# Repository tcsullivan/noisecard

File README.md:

# NoiseCard

NoiseCard is an attempt to build a dead easy tool for monitoring ambient noise levels. The ultra-low-power microcontroller takes periodic decibel measurements while powered on, using blinking LEDs for indication. The circuit requires only a few milliwatts to run, enabling it to run off of direct solar power without a battery (though some large capacitors provide a small reserve).

Ambient noise levels in populated areas, especially North America, can often exceed what is considered safe for our ears, with prolonged exposure leading to lasting impacts on our health. Through a tool like the NoiseCard, people can become more aware of the noisy environments they're living in (and potentially take action to reduce excess noise exposure).

## Building the source

You need:

* [ChibiOS sources](https://www.chibios.org/dokuwiki/doku.php)
* The arm-none-eabi GCC toolchain (through your distro or from [ARM developer](https://developer.arm.com/downloads/-/gnu-rm))
* [GNU Make](https://www.gnu.org/software/make/)
* [OpenOCD](https://openocd.org/) or another tool to program the microcontroller
* [KiCAD](https://www.kicad.org/) if you wish to work with the hardware files

Extract ChibiOS to a folder, edit the `Makefile` so CHIBIOS points to that folder, then run `make`.

### Flashing the card

You'll need a 6-pin Tag-Connect cable (e.g. [TC2030-CTX-NL](https://www.tag-connect.com/product/tc2030-ctx-nl-6-pin-no-legs-cable-with-10-pin-micro-connector-for-cortex-processors)), compatible programmer, and OpenOCD. Power up the card and run the following command (using the appropriate interface scripts for your programmer):

```
openocd -f interface/ftdi/olimex-arm-usb-ocd-h.cfg -f interface/ftdi/olimex-arm-jtag-swd.cfg -f target/stm32g0x.cfg -c "program build/ch.hex verify reset exit"
```

## Credits

* [ESP32-I2S-SLM](https://hackaday.io/project/166867-esp32-i2s-slm) for a starting point with accurate decibel-measuring code.
* [Qfplib](https://www.quinapalus.com/qfplib.html) for providing optimized floating-point code for the Cortex-M0+ microcontroller.
* ChibiOS for providing an awesome RTOS and HAL that made firmware porting and device configuration a breeze.

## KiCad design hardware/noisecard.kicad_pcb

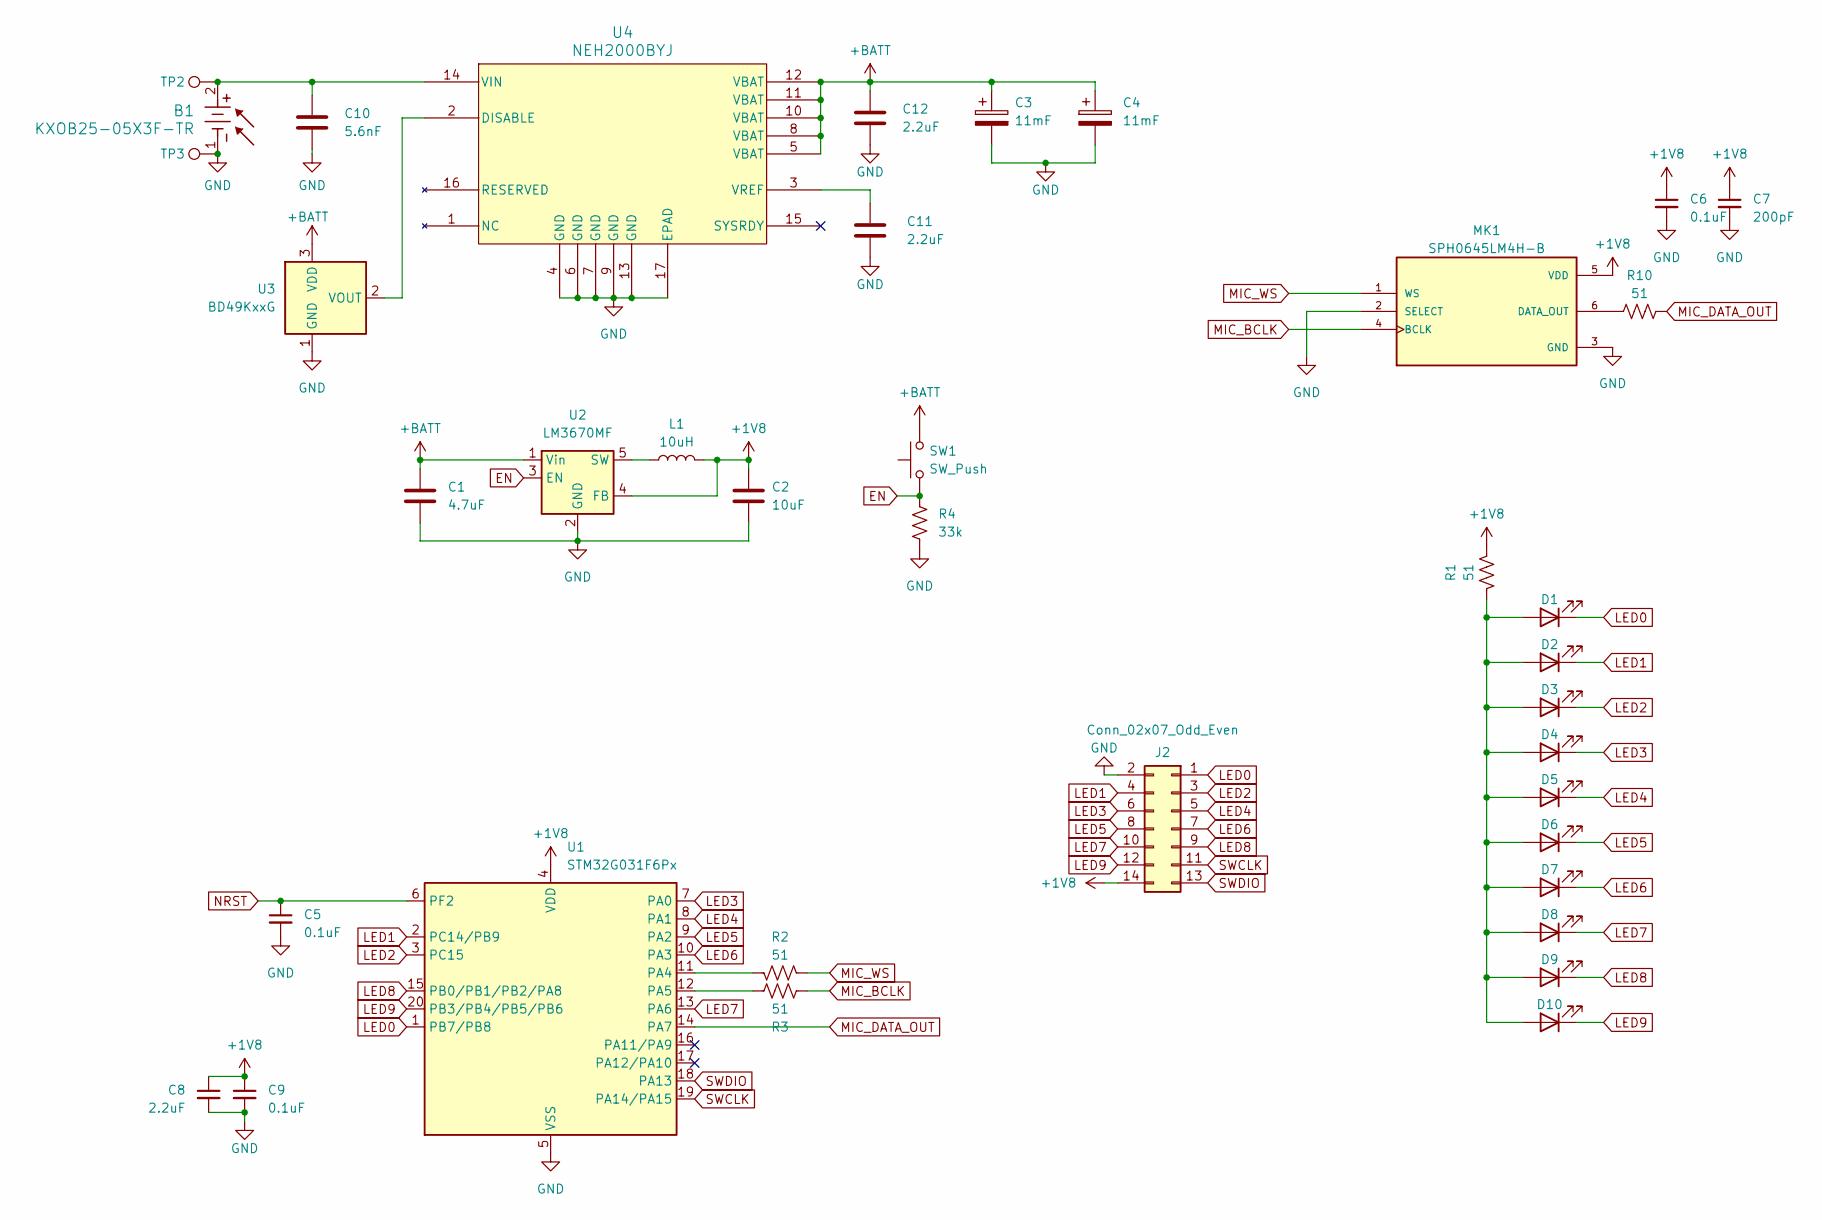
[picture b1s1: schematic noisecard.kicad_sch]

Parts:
B1: KXOB25-05X3F-TR; KXOB25-02X8F-TR_IXY; Part Number KXOB25-05X3F-TR
C1: 4.7uF; C_0805_2012Metric; Part Number CL21A475KAQNNNE
C2: 10uF; C_0805_2012Metric; Part Number CL21A106KOQNNNE
C3, C4: 11mF; C_1210_3225Metric; Part Number CPH3225A
C5, C6, C9: 0.1uF; C_0603_1608Metric; Part Number CC0603KRX7R6BB104
C7: 200pF; C_0603_1608Metric; Part Number 06033A201FAT2A
C8, C11, C12: 2.2uF; C_0805_2012Metric; Part Number CL21A225KBFNNNE
C10: 5.6nF; C_0603_1608Metric
D1, D2, D3, D4, D5, D6, D7, D8, D9, D10: LED; LED_0603_1608Metric; Part Number APTD1608LSURCK
J2: Conn_02x07_Odd_Even; PinHeader_2x07_P2.54mm_Vertical
L1: 10uH; L_0805_2012Metric; Part Number MLZ2012N100LT000
MK1: SPH0645LM4H-B; MIC_SPH0645LM4H-B; Part Number SPH0645LM4H-B
R1, R2, R3, R10: 51; R_0603_1608Metric; Part Number RC0603JR-0751RL
R4: 33k; R_0603_1608Metric
SW1: SW_Push; SW_SPST_EVQP0
TP2, TP3: TestPoint; TestPoint_THTPad_3.0x3.0mm_Drill1.5mm
U1: STM32G031F6Px; TSSOP-20_4.4x6.5mm_P0.65mm; Part Number STM32G031F6P6
U2: LM3670MF; TSOT-23-5; Part Number LM3670MF-1.8/NOPB
U3: BD49KxxG; SOT-23
U4: NEH2000BYJ; HWQFN16_SOT8076-1_NEX; Part Number NEH2000BYJ

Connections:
+1V8: C2.1, C6.1, C7.1, C8.1, C9.1, J2.14, L1.2, MK1.5 (VDD), R1.1, U1.4 (VDD), U2.4 (FB)
+BATT: C1.1, C3.1, C4.1, C12.1, SW1.2, U2.1 (Vin), U3.3 (VDD), U4.5 (VBAT), U4.8 (VBAT), U4.10 (VBAT), U4.11 (VBAT), U4.12 (VBAT)
EN: R4.2, SW1.1, U2.3 (EN)
GND: B1.1, C1.2, C2.2, C3.2, C4.2, C5.2, C6.2, C7.2, C8.2, C9.2, C10.2, C11.2, C12.2, J2.2, MK1.2 (SELECT), MK1.3 (GND), R4.1, TP3.1, U1.5 (VSS), U2.2 (GND), U3.1 (GND), U4.4 (GND), U4.6 (GND), U4.7 (GND), U4.9 (GND), U4.13 (GND), U4.17 (EPAD)
LED0: D1.1 (K), J2.1, U1.1 (PB7/PB8)
LED1: D2.1 (K), J2.4, U1.2 (PC14/PB9)
LED2: D3.1 (K), J2.3, U1.3 (PC15)
LED3: D4.1 (K), J2.6, U1.7 (PA0)
LED4: D5.1 (K), J2.5, U1.8 (PA1)
LED5: D6.1 (K), J2.8, U1.9 (PA2)
LED6: D7.1 (K), J2.7, U1.10 (PA3)
LED7: D8.1 (K), J2.10, U1.13 (PA6)
LED8: D9.1 (K), J2.9, U1.15 (PB0/PB1/PB2/PA8)
LED9: D10.1 (K), J2.12, U1.20 (PB3/PB4/PB5/PB6)
MIC_BCLK: MK1.4 (BCLK), R3.1
MIC_DATA_OUT: R10.2, U1.14 (PA7)
MIC_WS: MK1.1 (WS), R2.1
NRST: C5.1, U1.6 (PF2)
unnamed: D1.2 (A), D2.2 (A), D3.2 (A), D4.2 (A), D5.2 (A), D6.2 (A), D7.2 (A), D8.2 (A), D9.2 (A), D10.2 (A), R1.2
unnamed: MK1.6 (DATA_OUT), R10.1
unnamed: R2.2, U1.11 (PA4)
unnamed: R3.2, U1.12 (PA5)
unnamed: L1.1, U2.5 (SW)
unnamed: U3.2 (VOUT), U4.2 (DISABLE)
unnamed: B1.2, C10.1, TP2.1, U4.14 (VIN)
unnamed: C11.1, U4.3 (VREF)
SWCLK: J2.11, U1.19 (PA14/PA15)
SWDIO: J2.13, U1.18 (PA13)

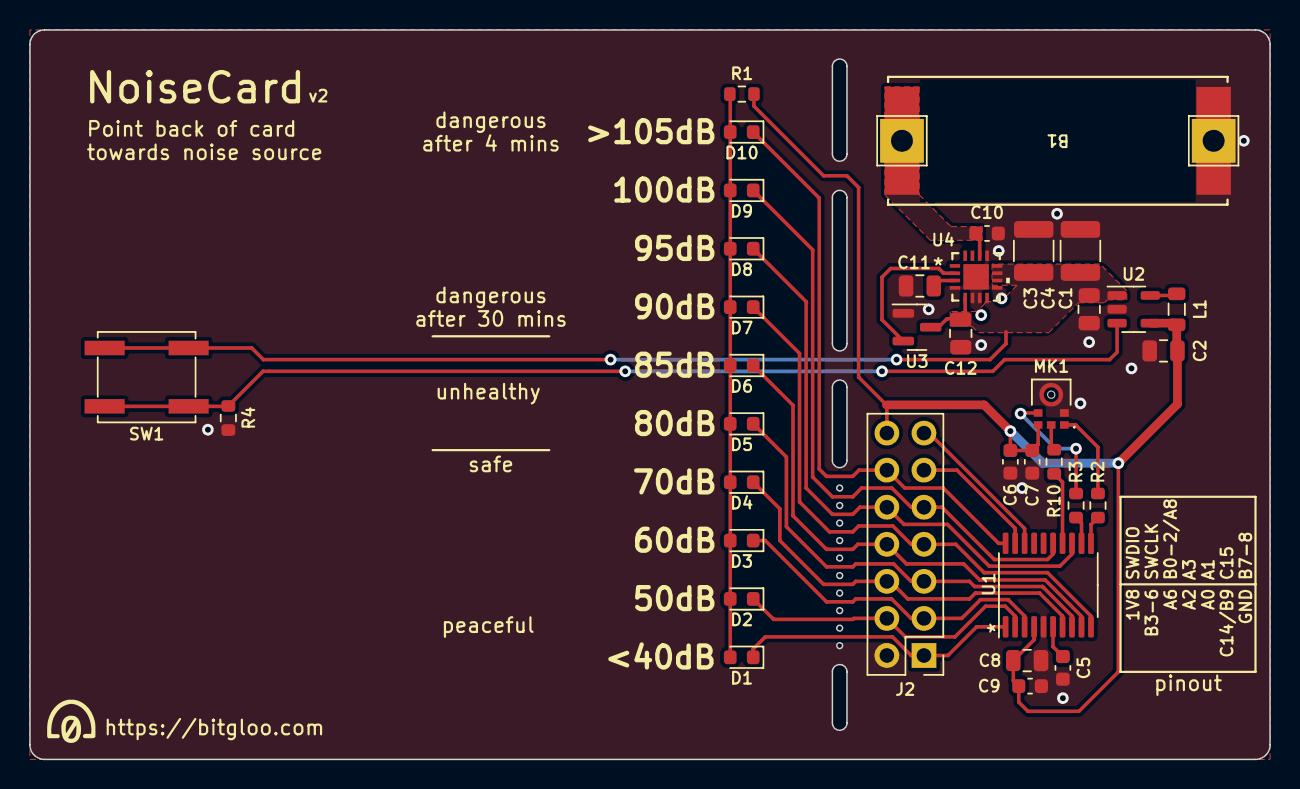
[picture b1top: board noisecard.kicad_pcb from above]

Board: 2 copper layers, 85.0 x 50.0 mm, 38 parts (0 on the bottom side), 28 nets.

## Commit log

2024-06-02 use qfplib; fix I2S clock
2024-06-05 fix qfplib dependence; clean up filter()
2024-06-05 add hardware files
2024-06-05 license source code
2024-06-05 add readme
2024-06-07 go os-less; filter in sram; consider dynamic freq
2024-06-08 sleeponexit; give up on fast clock
2024-06-08 wip: prep code for brief execution
    we do *not* have much power available
2024-06-10 schematic cleanup
2024-06-10 pcb firmware working
2024-06-10 stop using stride term
2024-06-10 move io config to board.c
2024-06-11 make led show a little longer
2024-06-11 add energy harvester and supercaps
2024-06-13 prune qfplib to save 4.5kB
2024-06-29 finish up rev2 design

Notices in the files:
hardware/noisecard.kicad_pcb:
Released under the CERN Open Hardware License Version 2 - Strongly Reciprocal
